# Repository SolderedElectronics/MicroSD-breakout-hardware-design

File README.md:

# microSD breakout Hardware design

## About the product

|  |
| :----------------------------------------------------------: |
|      [Buy microSD breakout](https://www.solde.red/333050)      |

A module which enables the use of micro SD cards with Arduino via SPI communication. You can save various types of data on the SD card, create logs, read the information from it or perform various actions.

## Repository contents

All Soldered Electronics hardware designed in KiCAD, and repositories are organized in the following way:

- CAD folder - contains KiCAD files (Schematics, Board, Panel Board), sorted by version. Change log lists all changes between versions.
- OUTPUTS - contains useful files, such as Bill of Materials (BOM), PDF of schematics, 3D .step file of the board and gerber files, sorted by version. 
- OUTPUTS -> Compliance - Certificates and useful legal stuff. 

## Want to contribute?

Please feel free to submit a pull request if you have any contributions. We encourage you to submit an issue or pull request if you find a bug. 

## About Soldered

At Soldered, we design and manufacture a wide selection of electronic products to help you turn your ideas into acts and bring you one step closer to your final project. Our products are intented for makers and crafted in-house by our experienced team in Osijek, Croatia. We believe that sharing is a crucial element for improvement and innovation, and we work hard to stay connected with all our makers regardless of their skill or experience level. Therefore, all our products are open-source. Finally, we always have your back. If you face any problem concerning either your shopping experience or your electronics project, our team will help you deal with it, offering efficient customer service and cost-free technical support anytime. Some of those might be useful for you:

- [Web Store](https://www.soldered.com/shop)
- [Tutorials & Projects](https://soldered.com/learn)
- [Community & Technical support](https://soldered.com/community)

## License info

All Soldered open-source hardware (OSH) is under The TAPR Open Hardware License. Read more in the LICENSE file. 

No warranty - all designs in this repository are distributed in the hope that they will be useful, but without any warranty. They are provided "AS IS", therefore without warranty of any kind, either expressed or implied. The entire quality and performance of what you do with the contents of this repository are your responsibility. In no event, Soldered Electronics will be liable for your damages, losses, including any general, special, incidental or consequential damage arising out of the use or inability to use the contents of this repository. 

## Have fun! 
And thank you from your fellow makers at Soldered Electronics.

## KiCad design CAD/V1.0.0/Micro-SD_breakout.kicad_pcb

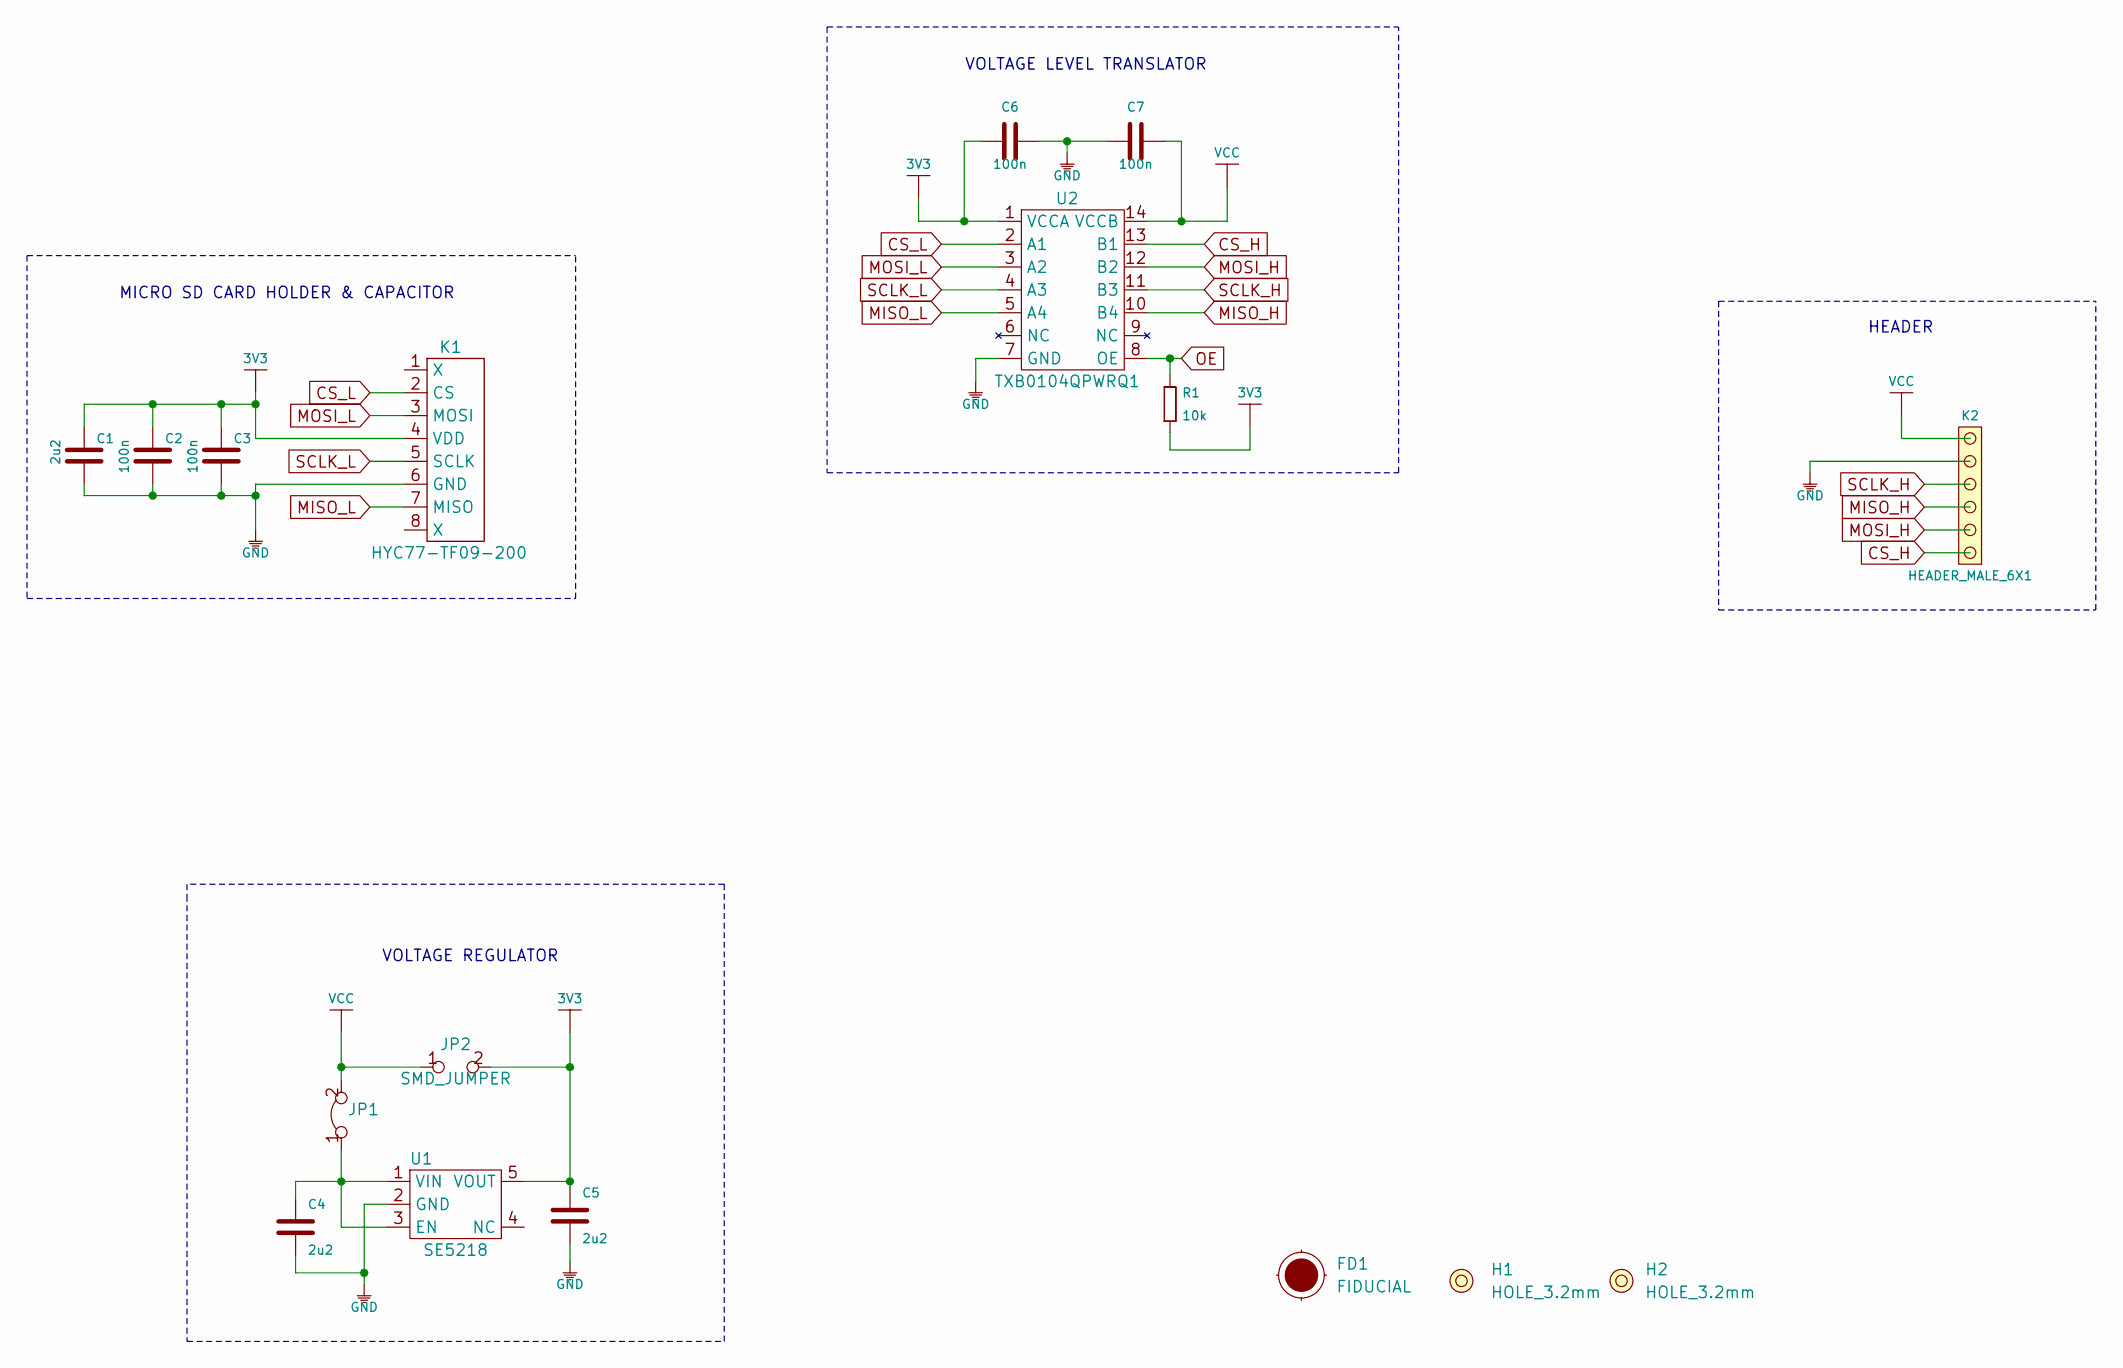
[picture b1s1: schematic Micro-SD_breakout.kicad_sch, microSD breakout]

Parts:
C1, C4, C5: 2u2; 0603C
C2, C3, C6, C7: 100n; 0603C
FD1: FIDUCIAL; FIDUCIAL_23
H1, H2: HOLE_3.2mm
JP1: SMD-JUMPER-CONNECTED_TRACE_SLODERMASK
JP2: SMD_JUMPER
K1: HYC77-TF09-200
K2: HEADER_MALE_6X1
R1: 10k; 0603R
U1: SE5218; SOT-23-5
U2: TXB0104QPWRQ1

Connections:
3V3: C1.2, C2.2, C3.2, C5.2, C6.1, JP2.2, K1.4 (VDD), R1.1, U1.5 (VOUT), U2.1 (VCCA)
CS_H: K2.1, U2.13 (B1)
CS_L: K1.2 (CS), U2.2 (A1)
GND: C1.1, C2.1, C3.1, C4.1, C5.1, C6.2, C7.1, K1.6 (GND), K2.5, U1.2 (GND), U2.7 (GND)
MISO_H: K2.3, U2.10 (B4)
MISO_L: K1.7 (MISO), U2.5 (A4)
MOSI_H: K2.2, U2.12 (B2)
MOSI_L: K1.3 (MOSI), U2.3 (A2)
unnamed: C4.2, JP1.1, U1.1 (VIN), U1.3 (EN)
OE: R1.2, U2.8 (OE)
SCLK_H: K2.4, U2.11 (B3)
SCLK_L: K1.5 (SCLK), U2.4 (A3)
VCC: C7.2, JP1.2, JP2.1, K2.6, U2.14 (VCCB)

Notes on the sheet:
VOLTAGE LEVEL TRANSLATOR
MICRO SD CARD HOLDER & CAPACITOR
VOLTAGE REGULATOR
HEADER

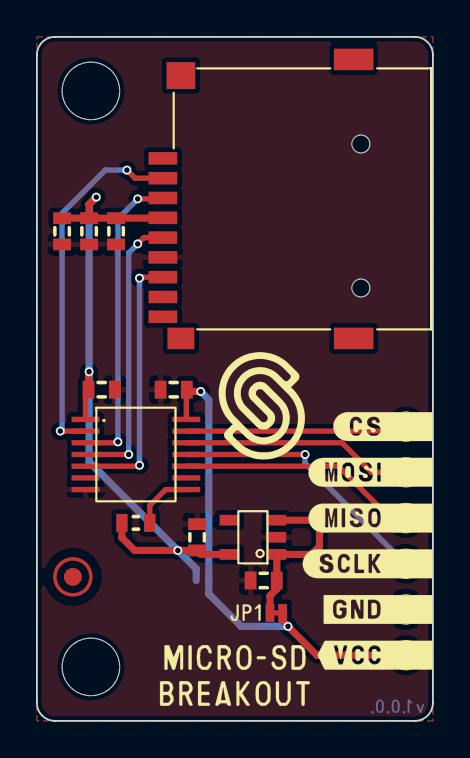
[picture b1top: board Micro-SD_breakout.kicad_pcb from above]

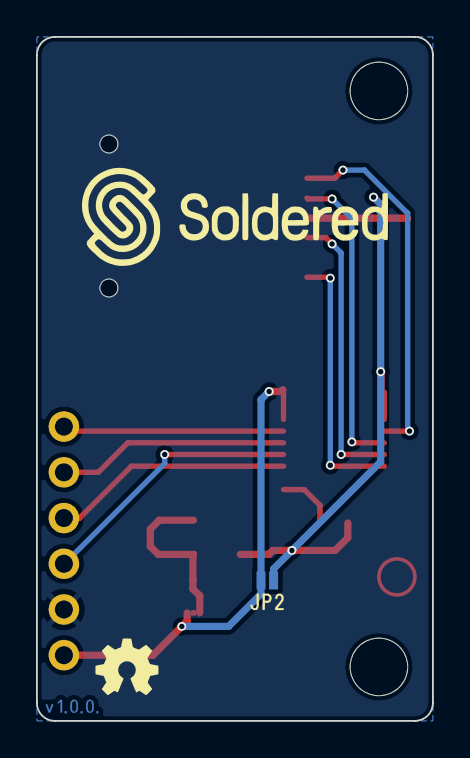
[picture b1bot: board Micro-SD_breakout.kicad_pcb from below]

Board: 2 copper layers, 22.0 x 38.0 mm, 18 parts (3 on the bottom side), 13 nets.

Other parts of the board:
Ref**: Val**; Version1.0.0.

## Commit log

2022-08-06 Updating open source files.
